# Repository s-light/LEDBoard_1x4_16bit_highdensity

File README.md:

<!--lint disable maximum-line-length-->
<!--lint disable list-item-spacing-->
<!--lint disable list-item-indent-->

# LED-Board 1x4 16bit high density

a LED Board that can be combined seamlessly to bigger lines with very high LED density (= small pixel-pitch).  
It uses the [TI TLC5971](http://www.ti.com/product/TLC5971) Constant-Current LED-Driver Chip with 16bit dimming resolution (HTSSOP-20 housing).  
The LED-Type used is [Nichia NSSM124D](http://www.nichia.co.jp/en/product/led_product_data.html?type=%27NSSM124D%27) - these are [available as cut-tape from an distributor](http://www.leds.de/en/Ordinary-LEDs/SMD-LEDs/Nichia-SMD-LED-RGB-NSSM124DT.html).

The thing is designed to be hand-soldered.

## Project-Status
- design phase

### TODO
- fix pads that are to small for hand-soldering
- order updated PCB's
- solder some more boards

## Technical Information
every controller chip (TLC5971) has 12 ConstantCurrent outputs. so every LED is controllable individual.

### HW
- PCB size: 12 x 8 x 3.3mm
- pixel-pitch: 3.1mm
- 3.8V..5.5V
- <= 0.25A (maximum)

<!--
### BOM
there is the raw exported BOM at [export/BOM/LEDBoard_4x4_16bit_BOM.csv](export/BOM/LEDBoard_4x4_16bit_BOM.csv) and an modified LibreOffice Calc file with ordering and Price calculations at [doc/LEDBoard_4x4_16bit_PriceCalculation_Ordering](doc/LEDBoard_4x4_16bit_PriceCalculation_Ordering.csv) (link points to exported csv as preview) -->

### controlling

see [LEDBoard_4x4_16bit](https://github.com/s-light/LEDBoard_4x4_16bit) for more Information

## KiCad Version
```text
Application: kicad
Version: 5.0.0-fee4fd1~66~ubuntu18.04.1, release build
Libraries:
    wxWidgets 3.0.4
    libcurl/7.58.0 OpenSSL/1.1.0g zlib/1.2.11 libidn2/2.0.4 libpsl/0.19.1 (+libidn2/2.0.4) nghttp2/1.30.0 librtmp/2.3
Platform: Linux 4.15.0-36-generic x86_64, 64 bit, Little endian, wxGTK
Build Info:
    wxWidgets: 3.0.4 (wchar_t,wx containers,compatible with 2.8) GTK+ 2.24
    Boost: 1.65.1
    OpenCASCADE Community Edition: 6.9.1
    Curl: 7.58.0
    Compiler: GCC 7.3.0 with C++ ABI 1011

Build settings:
    USE_WX_GRAPHICS_CONTEXT=OFF
    USE_WX_OVERLAY=OFF
    KICAD_SCRIPTING=ON
    KICAD_SCRIPTING_MODULES=ON
    KICAD_SCRIPTING_WXPYTHON=OFF
    KICAD_SCRIPTING_ACTION_MENU=ON
    BUILD_GITHUB_PLUGIN=ON
    KICAD_USE_OCE=ON
    KICAD_USE_OCC=OFF
    KICAD_SPICE=ON
```

## License
<!-- License info -->
<br />
<span xmlns:dct="http://purl.org/dc/terms/" property="dct:title">
    LEDBoard_1x4_16bit_highdensity
</span>
by
<a xmlns:cc="http://creativecommons.org/ns#" href="https://github.com/s-light/LEDBoard_4x4_16bit" property="cc:attributionName" rel="cc:attributionURL">
    Stefan Krüger (s-light)
</a>
is licensed under a
<a rel="license" href="http://creativecommons.org/licenses/by/4.0/">
    Creative Commons Attribution 4.0 International License
</a>.

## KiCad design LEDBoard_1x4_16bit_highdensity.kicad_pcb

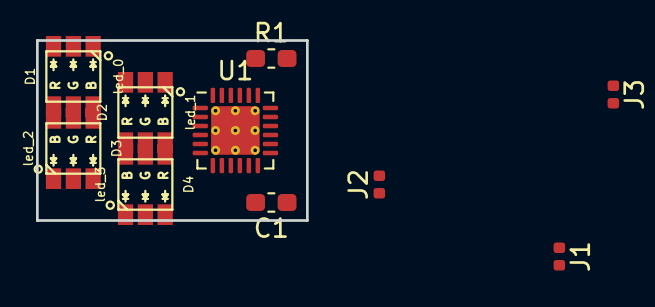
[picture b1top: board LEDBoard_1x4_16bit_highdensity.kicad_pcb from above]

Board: 2 copper layers, 15.0 x 10.0 mm, 10 parts (0 on the bottom side), 19 nets, no tracks yet.

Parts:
C1: 100n; C_0603_1608Metric_Pad1.05x0.95mm_HandSolder
D1: led_0; LED_NSSM124
D2: led_1; LED_NSSM124
D3: led_2; LED_NSSM124
D4: led_3; LED_NSSM124
J1: signal_in; R_0402_1005Metric
J2: signal_out; R_0402_1005Metric
J3: power; R_0402_1005Metric
R1: 2k7; R_0603_1608Metric_Pad1.05x0.95mm_HandSolder
U1: TLC5971PWP; Texas_RGE0024H_EP2.7x2.7mm_ThermalVias

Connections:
/clock_in: J1.2, U1.2
/clock_out: J2.1, U1.6
/data_in: J1.1, U1.1
/data_out: J2.2, U1.5
/led_0_b: D1.3, U1.21
/led_0_g: D1.2, U1.20
/led_0_r: D1.1, U1.19
/led_1_b: D2.3, U1.24
/led_1_g: D2.2, U1.23
/led_1_r: D2.1, U1.22
/led_2_b: D3.3, U1.9
/led_2_g: D3.2, U1.8
/led_2_r: D3.1, U1.7
/led_3_b: D4.3, U1.12
/led_3_g: D4.2, U1.11
/led_3_r: D4.1, U1.10
GND: C1.2, J3.1, R1.2, U1.18, U1.25
unnamed: R1.1, U1.16
VCC: C1.1, D1.4, D1.5, D1.6, D2.4, D2.5, D2.6, D3.4, D3.5, D3.6, D4.4, D4.5, D4.6, J3.2, U1.13, U1.15

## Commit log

2018-08-07 prepared repository
2018-08-07 started schematics
2018-08-07 rename
2018-08-07 first try on hd layout
2018-08-07 added hw pcb size
2018-08-27 basic component placement done
2018-08-27 placing & layout done :-)
2018-08-27 added 3d view
2018-08-27 partly routed
2018-09-11 first placement test
2018-10-13 prepared amulet version
2018-10-16 gitignore update added rescue.dcm
